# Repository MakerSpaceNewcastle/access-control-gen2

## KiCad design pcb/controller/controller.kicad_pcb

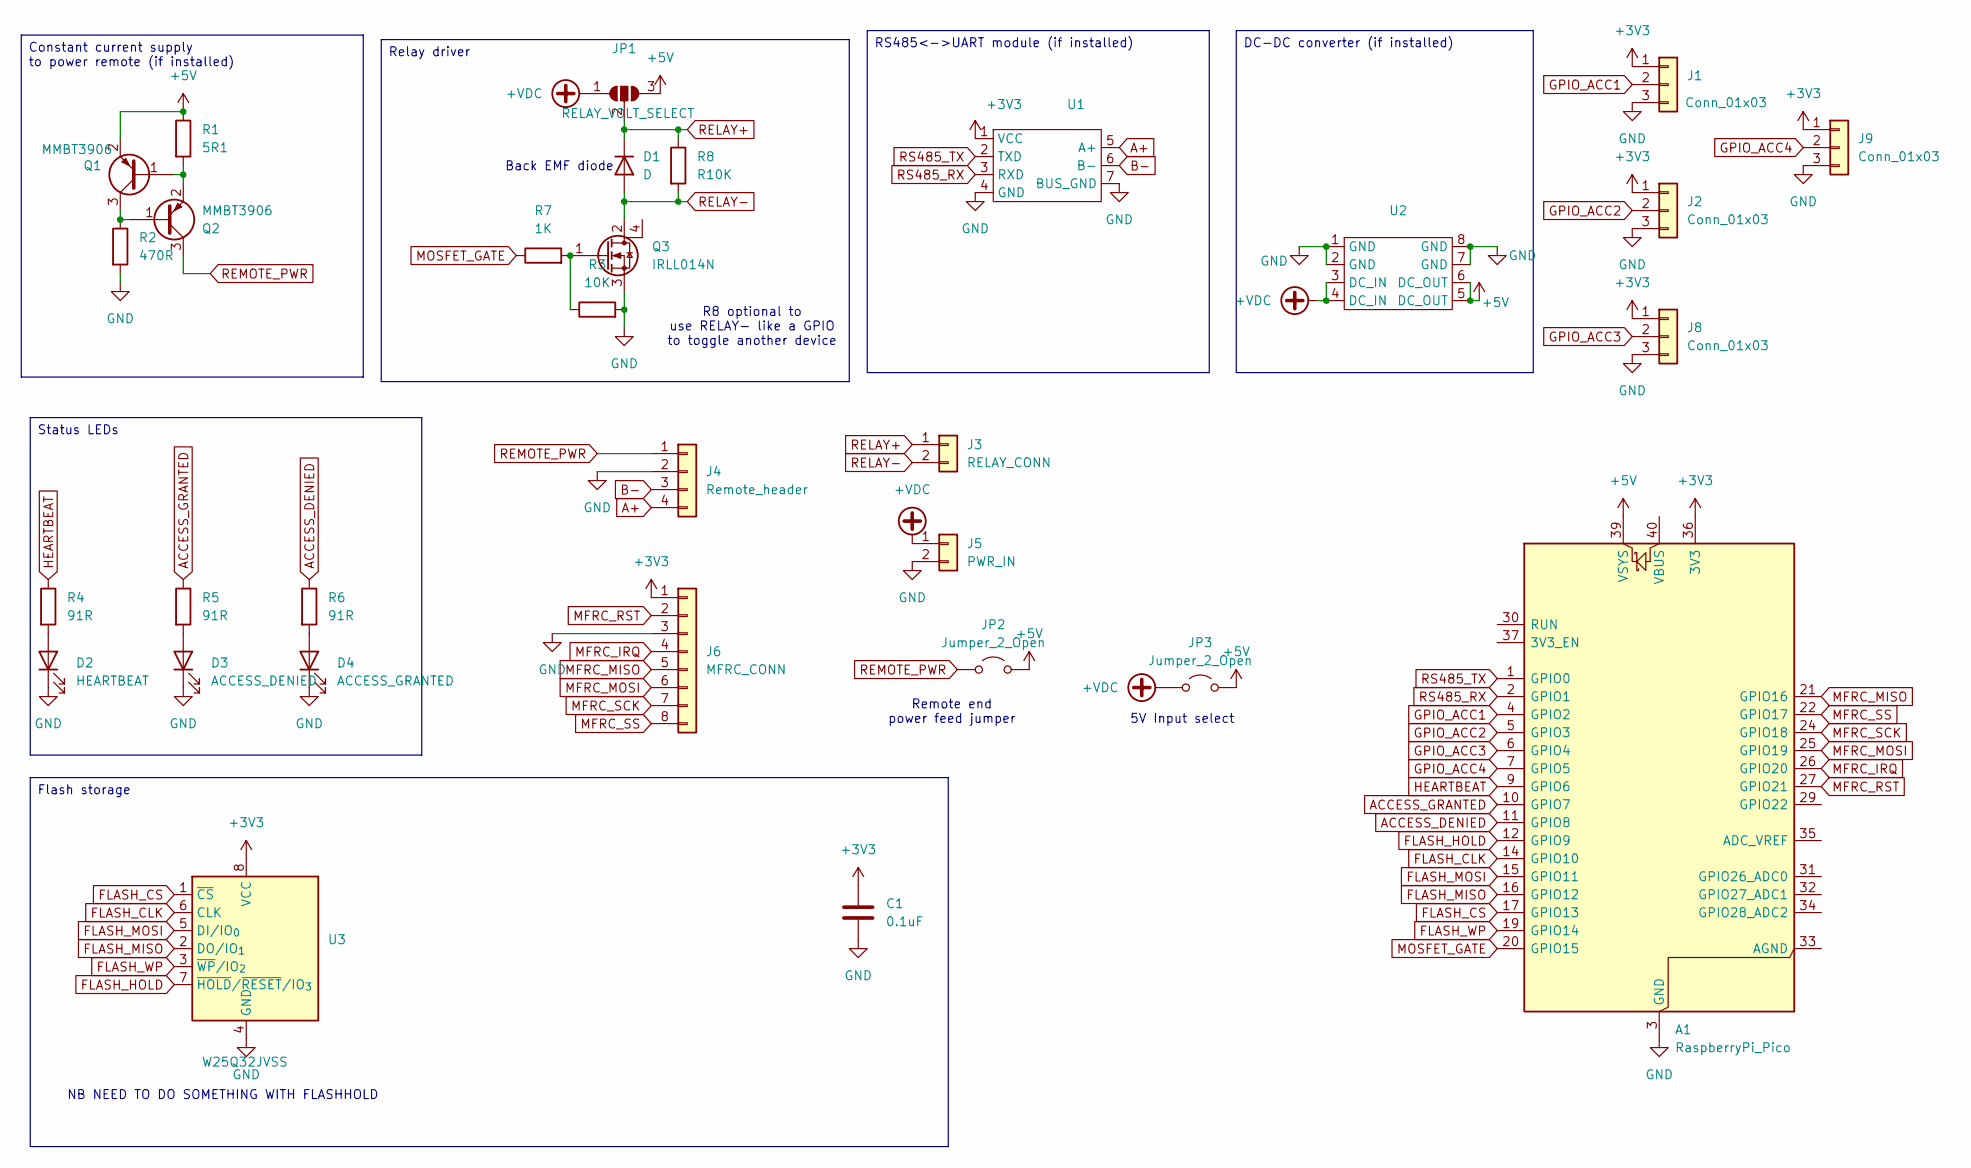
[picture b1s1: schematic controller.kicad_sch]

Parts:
A1: RaspberryPi_Pico; RaspberryPi_Pico_Common_Unspecified
C1: 0.1uF; C_1206_3216Metric_Pad1.33x1.80mm_HandSolder
D1: D; D_SMA-SMB_Universal_Handsoldering
D2: HEARTBEAT; LED_1206_3216Metric_Pad1.42x1.75mm_HandSolder
D3: ACCESS_DENIED; LED_1206_3216Metric_Pad1.42x1.75mm_HandSolder
D4: ACCESS_GRANTED; LED_1206_3216Metric_Pad1.42x1.75mm_HandSolder
J1, J2, J8, J9: Conn_01x03; JST_XH_B3B-XH-A_1x03_P2.50mm_Vertical
J3: RELAY_CONN; TerminalBlock_MetzConnect_Type059_RT06302HBWC_1x02_P3.50mm_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
J4: Remote_header; TerminalBlock_MetzConnect_Type059_RT06304HBWC_1x04_P3.50mm_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
J5: PWR_IN; TerminalBlock_MetzConnect_Type059_RT06302HBWC_1x02_P3.50mm_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
J6: MFRC_CONN; PinHeader_1x08_P2.54mm_Vertical
JP1: RELAY_VOLT_SELECT; SolderJumper-3_P1.3mm_Open_Pad1.0x1.5mm
JP2, JP3: Jumper_2_Open; SolderJumper-2_P1.3mm_Open_Pad1.0x1.5mm
Q1, Q2: MMBT3906; SOT-23
Q3: IRLL014N; SOT-223-3_TabPin2
R1: 5R1; R_1210_3225Metric_Pad1.30x2.65mm_HandSolder
R2: 470R; R_1210_3225Metric_Pad1.30x2.65mm_HandSolder
R3: 10K; R_1210_3225Metric_Pad1.30x2.65mm_HandSolder
R4, R5, R6: 91R; R_1210_3225Metric_Pad1.30x2.65mm_HandSolder
R7: 1K; R_1210_3225Metric_Pad1.30x2.65mm_HandSolder
R8: R10K; R_1210_3225Metric_Pad1.30x2.65mm_HandSolder
U1: RS485_to_ttl
U2: hw-1338
U3: W25Q32JVSS; SOIC-8_5.3x5.3mm_P1.27mm

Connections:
+3V3: A1.36 (3V3), C1.1, J1.1, J2.1, J6.1, J8.1, J9.1, U1.1 (VCC), U3.8 (VCC)
+5V: A1.39 (VSYS), JP1.3 (B), JP2.2 (B), JP3.2 (B), Q1.2 (E), R1.1, U2.5 (DC_OUT), U2.6 (DC_OUT)
+VDC: J5.1, JP1.1 (A), JP3.1 (A), U2.3 (DC_IN), U2.4 (DC_IN)
A+: J4.4, U1.5 (A+)
ACCESS_DENIED: A1.11 (GPIO8), R6.1
ACCESS_GRANTED: A1.10 (GPIO7), R5.1
B-: J4.3, U1.6 (B-)
FLASH_CLK: A1.14 (GPIO10), U3.6 (CLK)
FLASH_CS: A1.17 (GPIO13), U3.1 (~CS)
FLASH_HOLD: A1.12 (GPIO9), U3.7 (~HOLD/~RESET/IO_{3})
FLASH_MISO: A1.16 (GPIO12), U3.2 (DO/IO_{1})
FLASH_MOSI: A1.15 (GPIO11), U3.5 (DI/IO_{0})
FLASH_WP: A1.19 (GPIO14), U3.3 (~WP/IO_{2})
GND: A1.3 (GND), A1.8 (GND), A1.13 (GND), A1.18 (GND), A1.23 (GND), A1.28 (GND), A1.38 (GND), C1.2, D2.1 (K), D3.1 (K), D4.1 (K), J1.3, J2.3, J4.2, J5.2, J6.3, J8.3, J9.3, Q3.3 (S), R2.2, R3.2, U1.4 (GND), U1.7 (BUS_GND), U2.1 (GND), U2.2 (GND), U2.7 (GND), U2.8 (GND), U3.4 (GND)
GPIO_ACC1: A1.4 (GPIO2), J1.2
GPIO_ACC2: A1.5 (GPIO3), J2.2
GPIO_ACC3: A1.6 (GPIO4), J8.2
GPIO_ACC4: A1.7 (GPIO5), J9.2
HEARTBEAT: A1.9 (GPIO6), R4.1
MFRC_IRQ: A1.26 (GPIO20), J6.4
MFRC_MISO: A1.21 (GPIO16), J6.5
MFRC_MOSI: A1.25 (GPIO19), J6.6
MFRC_RST: A1.27 (GPIO21), J6.2
MFRC_SCK: A1.24 (GPIO18), J6.7
MFRC_SS: A1.22 (GPIO17), J6.8
MOSFET_GATE: A1.20 (GPIO15), R7.1
unnamed: D2.2 (A), R4.2
unnamed: D3.2 (A), R5.2
unnamed: D4.2 (A), R6.2
unnamed: Q1.1 (B), Q2.2 (E), R1.2
unnamed: Q1.3 (C), Q2.1 (B), R2.1
unnamed: Q3.1 (G), R3.1, R7.2
RELAY+: D1.1 (K), J3.1, JP1.2 (C), R8.1
RELAY-: D1.2 (A), J3.2, Q3.2 (D), R8.2
REMOTE_PWR: J4.1, JP2.1 (A), Q2.3 (C)
RS485_RX: A1.2 (GPIO1), U1.3 (RXD)
RS485_TX: A1.1 (GPIO0), U1.2 (TXD)

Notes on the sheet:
NB NEED TO DO SOMETHING WITH FLASHHOLD
Back EMF diode
R8 optional to use RELAY- like a GPIO to toggle another device
Remote end power feed jumper
5V Input select
Status LEDs
DC-DC converter (if installed)
Relay driver
RS485<->UART module (if installed)
Flash storage
Constant current supply to power remote (if installed)

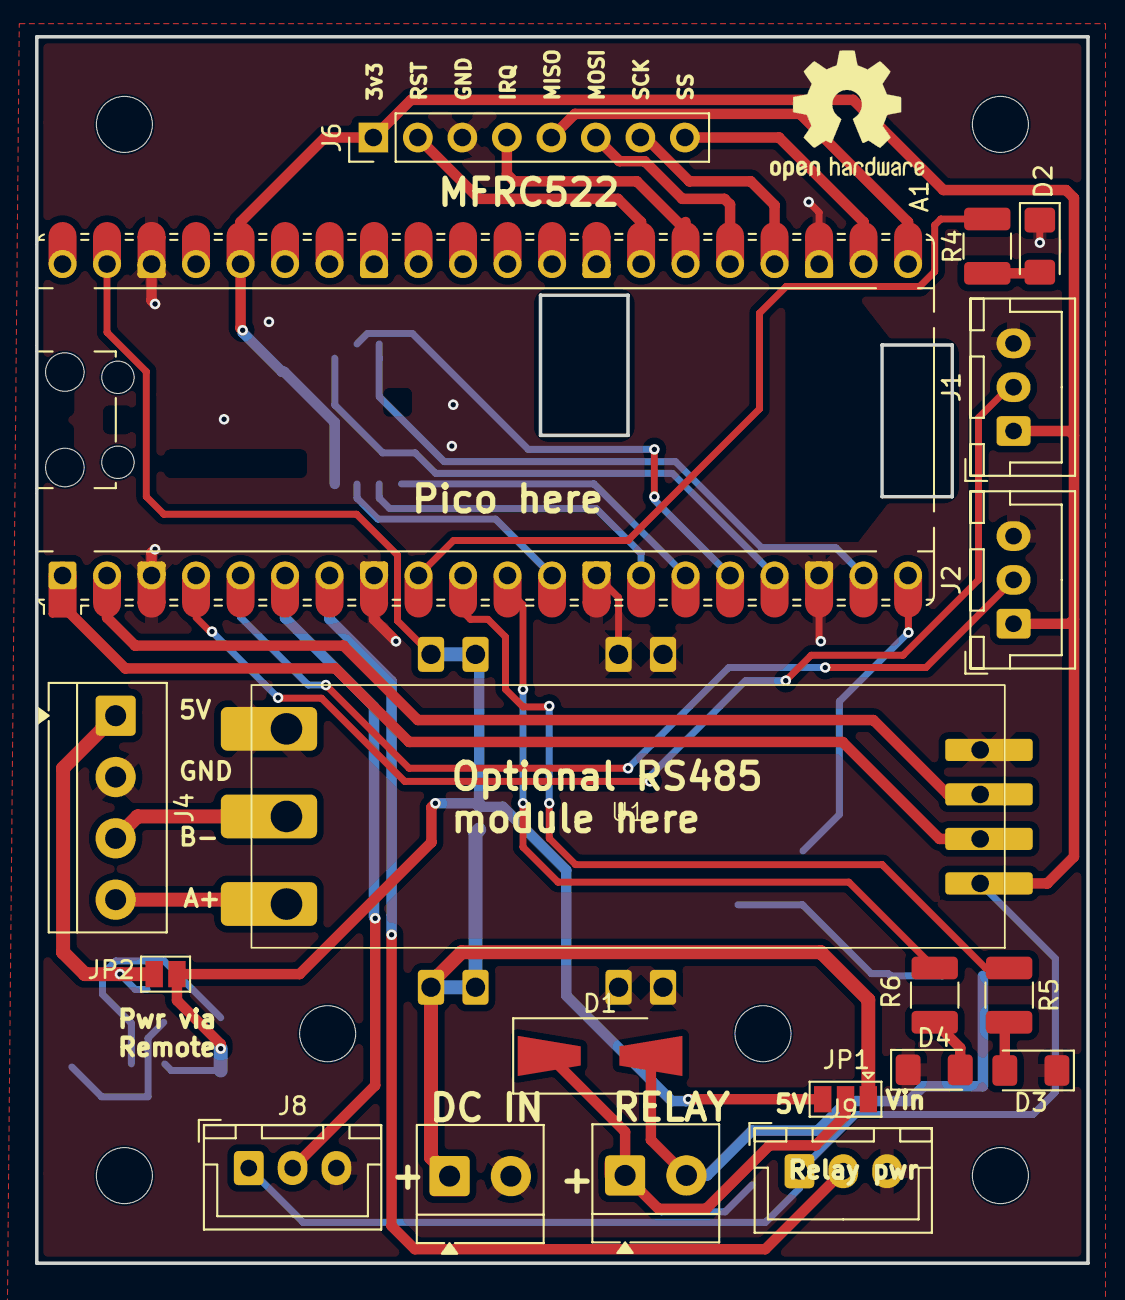
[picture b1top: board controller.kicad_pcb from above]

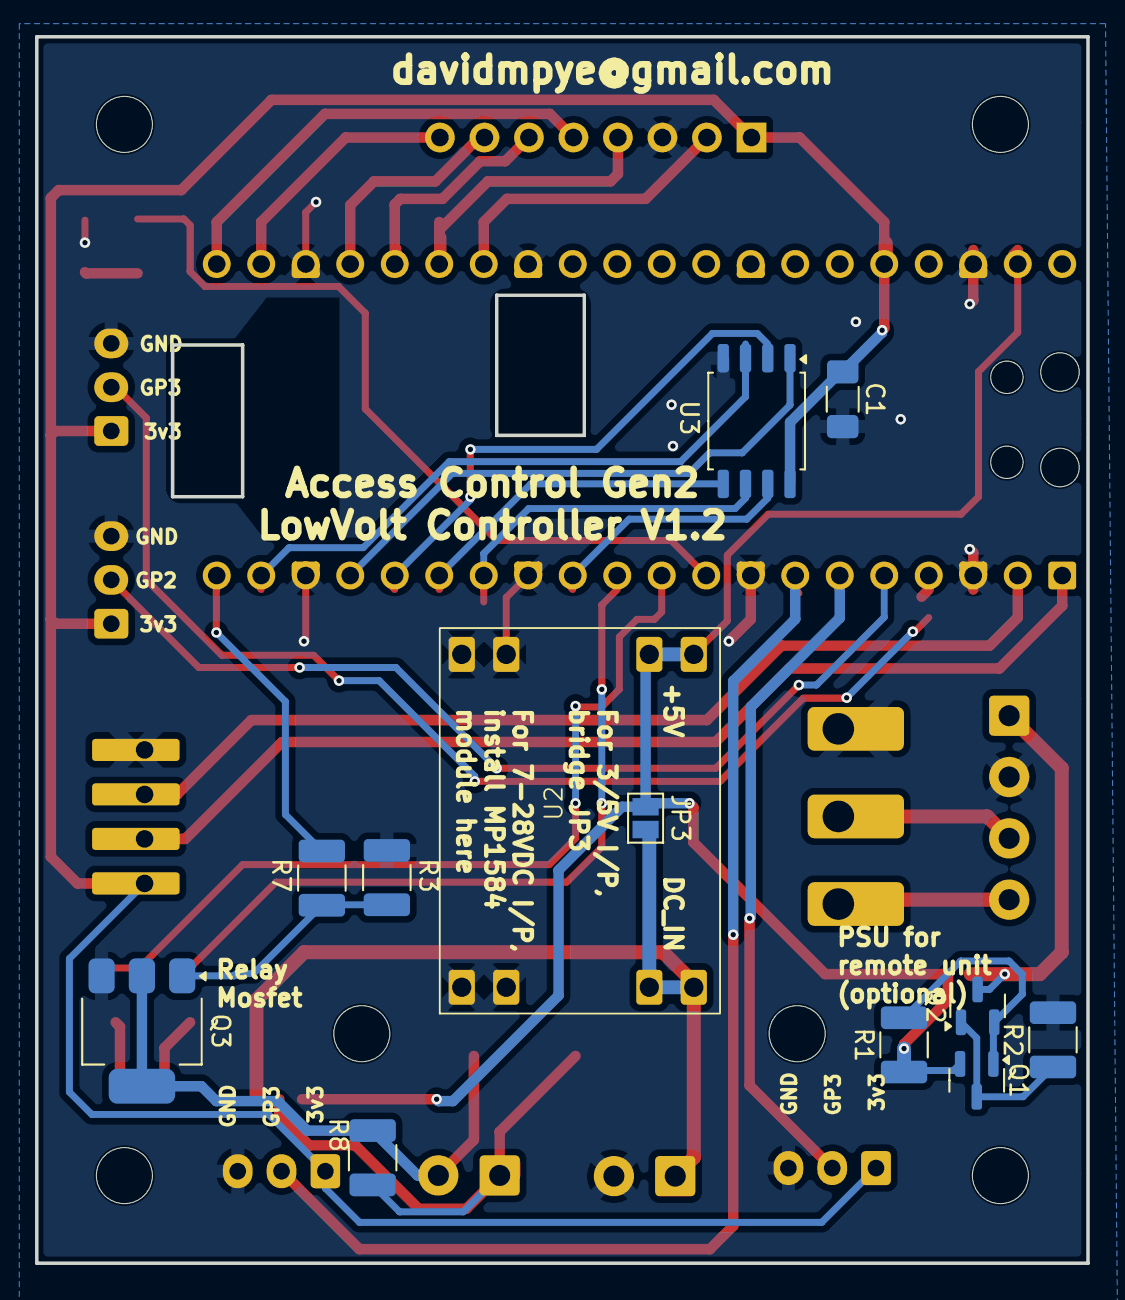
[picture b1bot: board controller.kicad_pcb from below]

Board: 2 copper layers, 60.0 x 70.0 mm, 31 parts (12 on the bottom side), 37 nets.

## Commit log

2026-01-06 Stop building a new client each sync attempt
2026-01-07 Make watchdog led less irritating (take 1)
2026-01-09 Change log task logic to ensure that HttpClient persists
2026-01-13 Updated pillarx
2026-05-10 Change runner to picotool + add .cargo file for main fw folder
2026-05-28 Add missing gitignore for KiCad projects
2026-05-30 Add enclosure for LV controller
2026-06-02 Update to kicad10 format
2026-06-03 Change footprint to use through-hole, add Edge.cuts cutout for debug pins.
2026-06-03 PCB tweaks
2026-06-03 Update pcby
2026-06-04 Track rerouting
2026-06-05 More minor PCB tweaks
2026-06-09 Correct LV enclosure back spacing
2026-06-13 Add wifi_reconnect_task
2026-06-13 Add wifi_reconnect_task (#1)
